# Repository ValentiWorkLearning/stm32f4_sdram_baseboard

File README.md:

# stm32f4_sdram_baseboard

The board which is based on STM32F446ZE MCU in BGA with the external SDRAM and BMI270 IMU.

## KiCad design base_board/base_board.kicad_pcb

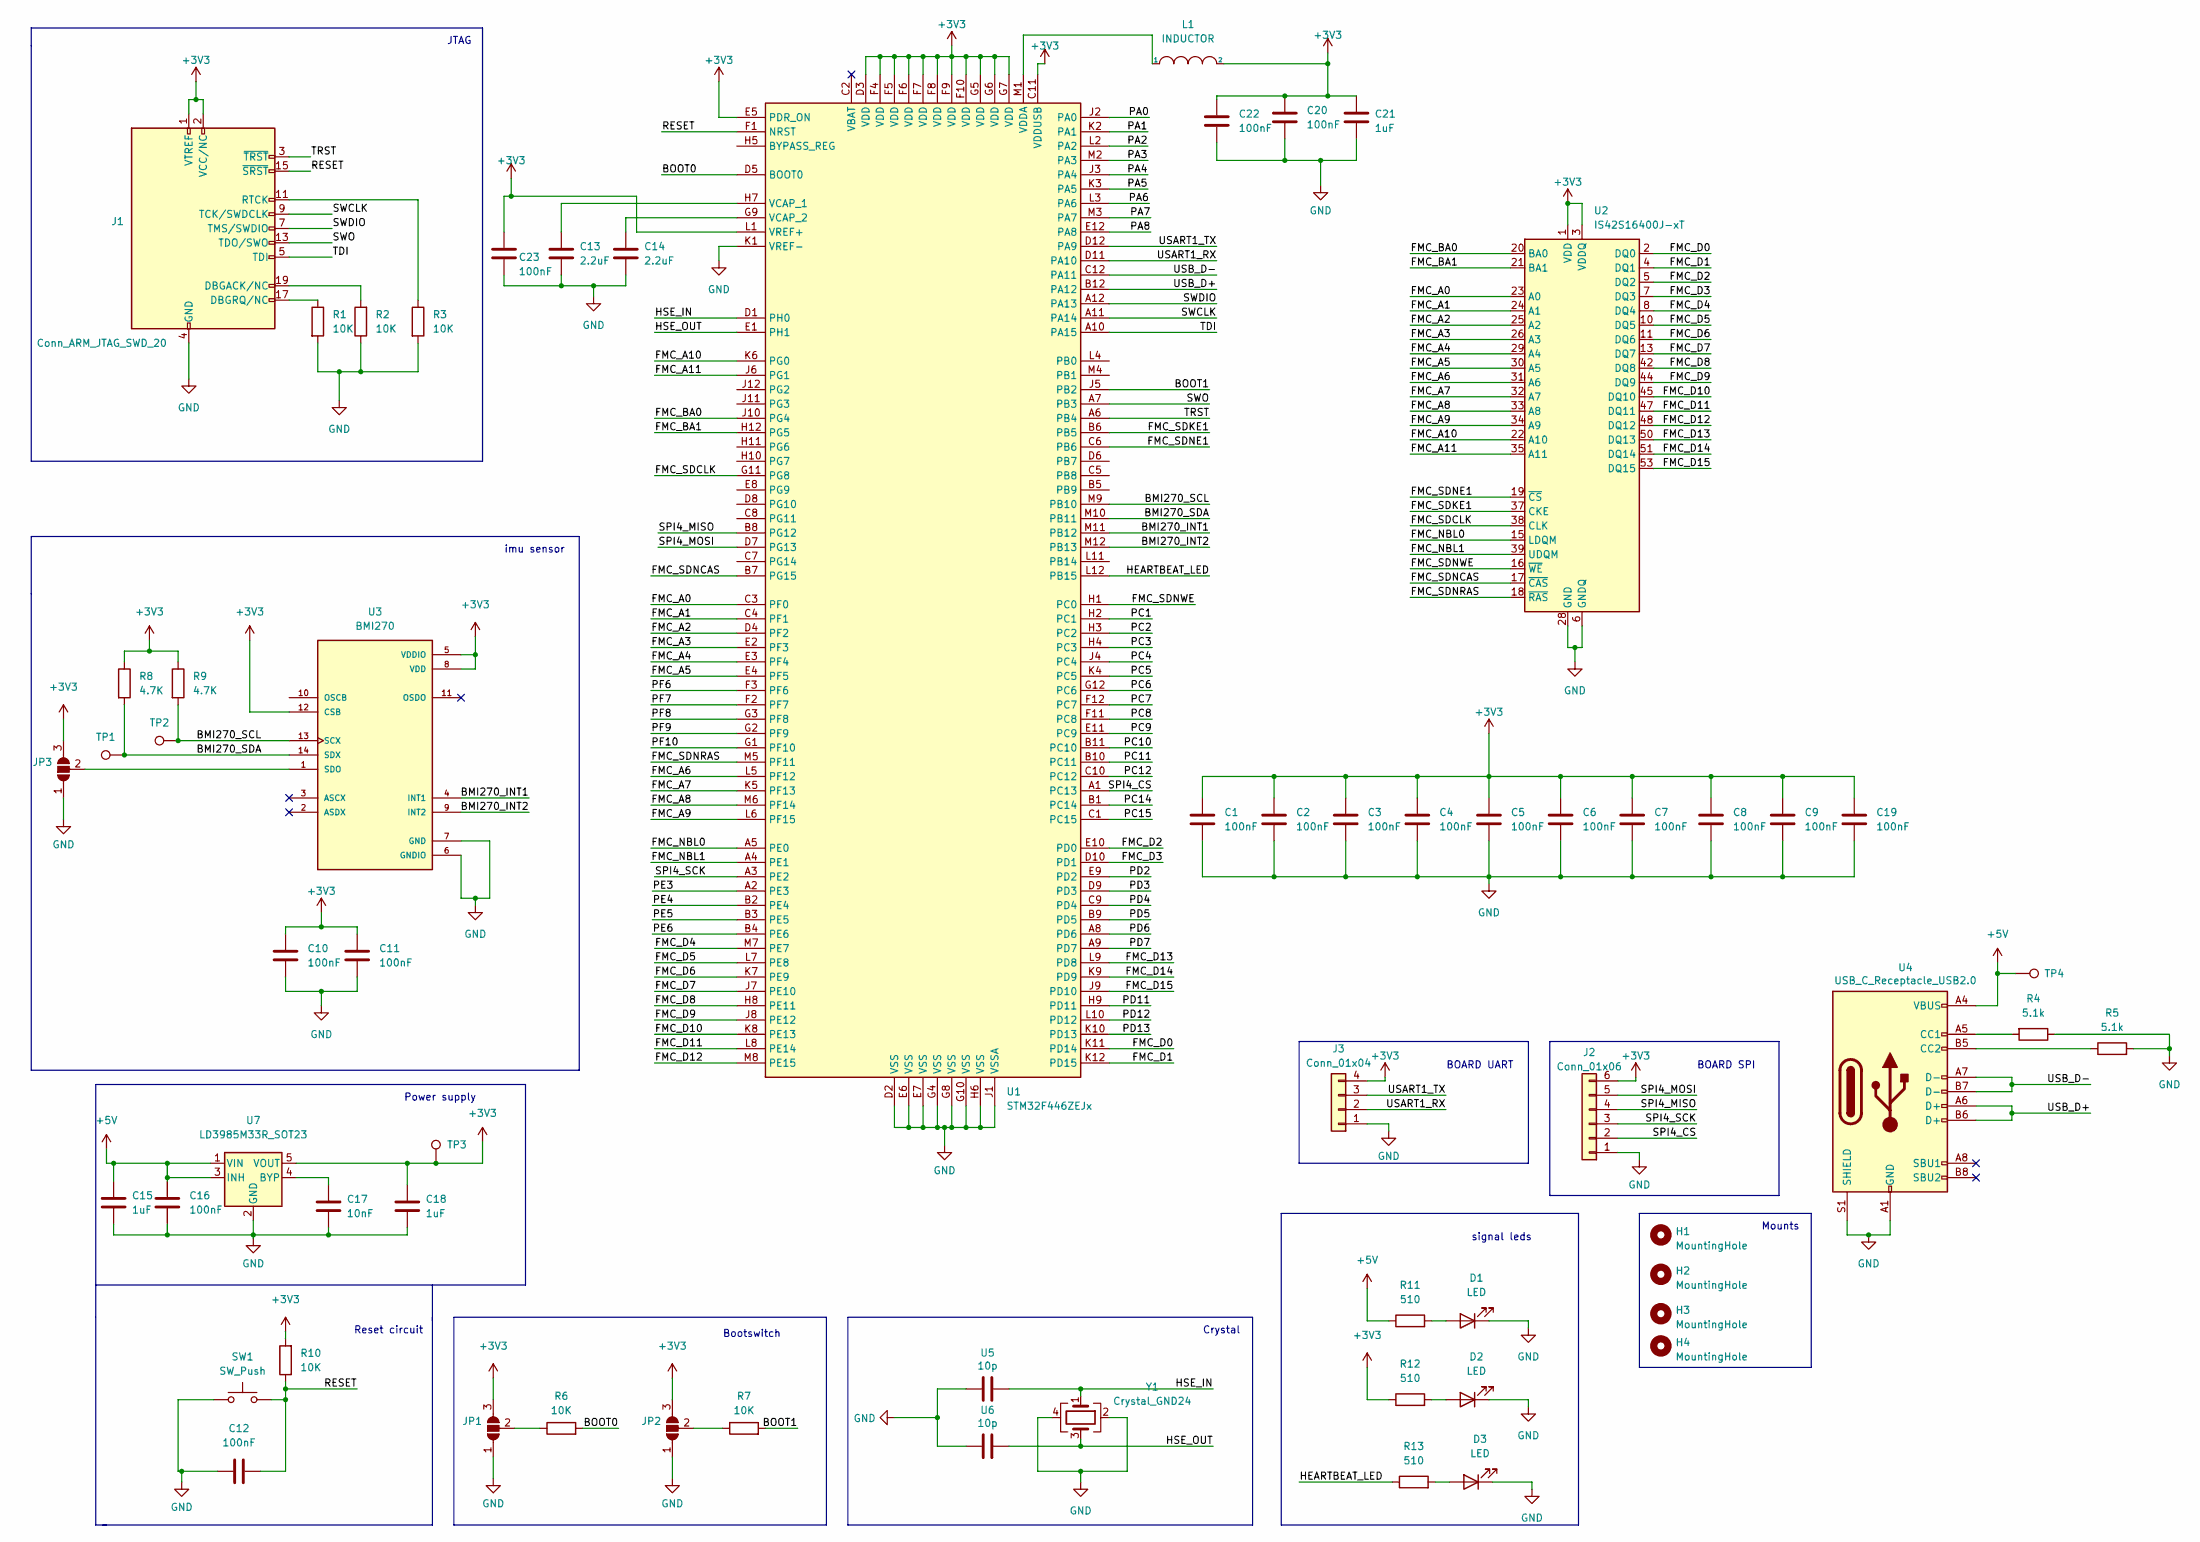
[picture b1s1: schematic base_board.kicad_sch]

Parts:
C1, C2, C3, C4, C5, C6, C7, C8, C9, C10, C11, C12, C16, C19, C20, C22, C23: 100nF; C_0603_1608Metric
C13, C14: 2.2uF; C_0603_1608Metric
C15, C18, C21: 1uF; C_0603_1608Metric
C17: 10nF; C_0603_1608Metric
D1, D2, D3: LED; LED_0603_1608Metric
H1, H2, H3, H4: MountingHole; MountingHole_3.2mm_M3
J1: Conn_ARM_JTAG_SWD_20; PinSocket_2x10_P2.54mm_Vertical
J2: Conn_01x06; PinHeader_1x06_P2.54mm_Vertical
J3: Conn_01x04; PinHeader_1x04_P2.54mm_Vertical
JP1, JP2, JP3: SolderJumper_3_Open; SolderJumper-3_P1.3mm_Open_RoundedPad1.0x1.5mm
L1: INDUCTOR; L_0603_1608Metric
R1, R2, R3, R6, R7, R10: 10K; R_0603_1608Metric
R4, R5: 5.1k; R_0603_1608Metric
R8, R9: 4.7K; R_0603_1608Metric
R11, R12, R13: 510; R_0603_1608Metric
SW1: SW_Push; SW_Push_1P1T_NO_6x6mm_H9.5mm
TP1, TP2, TP3, TP4: TestPoint; TestPoint_Pad_D3.0mm
U1: STM32F446ZEJx; UFBGA-144_10x10mm_Layout12x12_P0.8mm
U2: IS42S16400J-xT; TSOP-II-54_22.2x10.16mm_P0.8mm
U3: BMI270; XDCR_BMI270
U4: USB_C_Receptacle_USB2.0; USB_C_Receptacle_XKB_U262-16XN-4BVC11; LCSC C319148
U5, U6: 10p; C_0603_1608Metric; LCSC C32949
U7: LD3985M33R_SOT23; SOT-23-5
Y1: Crystal_GND24; Crystal_SMD_3225-4Pin_3.2x2.5mm

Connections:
+3V3: C1.1, C2.1, C3.1, C4.1, C5.1, C6.1, C7.1, C8.1, C9.1, C10.2, C11.2, C18.1, C19.1, C20.1, C21.1, C22.1, C23.1, J1.1 (VTREF), J1.2 (VCC/NC), J2.6, J3.4, JP1.3 (B), JP2.3 (B), JP3.3 (B), L1.2, R8.1, R9.1, R10.2, R12.1, TP3.1, U1.C11 (VDDUSB), U1.D3 (VDD), U1.E5 (PDR_ON), U1.F4 (VDD), U1.F5 (VDD), U1.F6 (VDD), U1.F7 (VDD), U1.F8 (VDD), U1.F9 (VDD), U1.F10 (VDD), U1.G5 (VDD), U1.G6 (VDD), U1.G7 (VDD), U1.L1 (VREF+), U2.1 (VDD), U2.3 (VDDQ), U2.9 (VDDQ), U2.14 (VDD), U2.27 (VDD), U2.43 (VDDQ), U2.49 (VDDQ), U3.5 (VDDIO), U3.8 (VDD), U3.12 (CSB), U7.5 (VOUT)
+5V: C15.1, C16.2, R11.1, TP4.1, U4.A4 (VBUS), U4.A9 (VBUS), U4.B4 (VBUS), U4.B9 (VBUS), U7.1 (VIN), U7.3 (INH)
/BMI270_INT1: U1.M11 (PB12), U3.4 (INT1)
/BMI270_INT2: U1.M12 (PB13), U3.9 (INT2)
/BMI270_SCL: R9.2, TP2.1, U1.M9 (PB10), U3.13 (SCX)
/BMI270_SDA: R8.2, TP1.1, U1.M10 (PB11), U3.14 (SDX)
/BOOT0: R6.2, U1.D5 (BOOT0)
/BOOT1: R7.2, U1.J5 (PB2)
/FMC_A0: U1.C3 (PF0), U2.23 (A0)
/FMC_A1: U1.C4 (PF1), U2.24 (A1)
/FMC_A2: U1.D4 (PF2), U2.25 (A2)
/FMC_A3: U1.E2 (PF3), U2.26 (A3)
/FMC_A4: U1.E3 (PF4), U2.29 (A4)
/FMC_A5: U1.E4 (PF5), U2.30 (A5)
/FMC_A6: U1.L5 (PF12), U2.31 (A6)
/FMC_A7: U1.K5 (PF13), U2.32 (A7)
/FMC_A8: U1.M6 (PF14), U2.33 (A8)
/FMC_A9: U1.L6 (PF15), U2.34 (A9)
/FMC_A10: U1.K6 (PG0), U2.22 (A10)
/FMC_A11: U1.J6 (PG1), U2.35 (A11)
/FMC_BA0: U1.J10 (PG4), U2.20 (BA0)
/FMC_BA1: U1.H12 (PG5), U2.21 (BA1)
/FMC_D0: U1.K11 (PD14), U2.2 (DQ0)
/FMC_D1: U1.K12 (PD15), U2.4 (DQ1)
/FMC_D2: U1.E10 (PD0), U2.5 (DQ2)
/FMC_D3: U1.D10 (PD1), U2.7 (DQ3)
/FMC_D4: U1.M7 (PE7), U2.8 (DQ4)
/FMC_D5: U1.L7 (PE8), U2.10 (DQ5)
/FMC_D6: U1.K7 (PE9), U2.11 (DQ6)
/FMC_D7: U1.J7 (PE10), U2.13 (DQ7)
/FMC_D8: U1.H8 (PE11), U2.42 (DQ8)
/FMC_D9: U1.J8 (PE12), U2.44 (DQ9)
/FMC_D10: U1.K8 (PE13), U2.45 (DQ10)
/FMC_D11: U1.L8 (PE14), U2.47 (DQ11)
/FMC_D12: U1.M8 (PE15), U2.48 (DQ12)
/FMC_D13: U1.L9 (PD8), U2.50 (DQ13)
/FMC_D14: U1.K9 (PD9), U2.51 (DQ14)
/FMC_D15: U1.J9 (PD10), U2.53 (DQ15)
/FMC_NBL0: U1.A5 (PE0), U2.15 (LDQM)
/FMC_NBL1: U1.A4 (PE1), U2.39 (UDQM)
/FMC_SDCLK: U1.G11 (PG8), U2.38 (CLK)
/FMC_SDKE1: U1.B6 (PB5), U2.37 (CKE)
/FMC_SDNCAS: U1.B7 (PG15), U2.17 (~CAS)
/FMC_SDNE1: U1.C6 (PB6), U2.19 (~CS)
/FMC_SDNRAS: U1.M5 (PF11), U2.18 (~RAS)
/FMC_SDNWE: U1.H1 (PC0), U2.16 (~WE)
/HEARTBEAT_LED: R13.1, U1.L12 (PB15)
/HSE_IN: U1.D1 (PH0), U5.1, Y1.1
/HSE_OUT: U1.E1 (PH1), U6.1, Y1.3
/PA0: U1.J2 (PA0)
/PA1: U1.K2 (PA1)
/PA2: U1.L2 (PA2)
/PA3: U1.M2 (PA3)
/PA4: U1.J3 (PA4)
/PA5: U1.K3 (PA5)
/PA6: U1.L3 (PA6)
/PA7: U1.M3 (PA7)
/PA8: U1.E12 (PA8)
/PC1: U1.H2 (PC1)
/PC2: U1.H3 (PC2)
/PC3: U1.H4 (PC3)
/PC4: U1.J4 (PC4)
/PC5: U1.K4 (PC5)
/PC6: U1.G12 (PC6)
/PC7: U1.F12 (PC7)
/PC8: U1.F11 (PC8)
/PC9: U1.E11 (PC9)
/PC10: U1.B11 (PC10)
/PC11: U1.B10 (PC11)
/PC12: U1.C10 (PC12)
/PC14: U1.B1 (PC14)
/PC15: U1.C1 (PC15)
/PD2: U1.E9 (PD2)
/PD3: U1.D9 (PD3)
/PD4: U1.C9 (PD4)
/PD5: U1.B9 (PD5)
/PD6: U1.A8 (PD6)
/PD7: U1.A9 (PD7)
/PD11: U1.H9 (PD11)
/PD12: U1.L10 (PD12)
/PD13: U1.K10 (PD13)
/PE3: U1.A2 (PE3)
/PE4: U1.B2 (PE4)
/PE5: U1.B3 (PE5)
/PE6: U1.B4 (PE6)
/PF6: U1.F3 (PF6)
/PF7: U1.F2 (PF7)
/PF8: U1.G3 (PF8)
/PF9: U1.G2 (PF9)
/PF10: U1.G1 (PF10)
/RESET: C12.1, J1.15 (~SRST), R10.1, SW1.2, U1.F1 (NRST)
/SPI4_CS: J2.2, U1.A1 (PC13)
/SPI4_MISO: J2.4, U1.B8 (PG12)
/SPI4_MOSI: J2.5, U1.D7 (PG13)
/SPI4_SCK: J2.3, U1.A3 (PE2)
/SWCLK: J1.9 (TCK/SWDCLK), U1.A11 (PA14)
/SWDIO: J1.7 (TMS/SWDIO), U1.A12 (PA13)
/SWO: J1.13 (TDO/SWO), U1.A7 (PB3)
/TDI: J1.5 (TDI), U1.A10 (PA15)
/TRST: J1.3 (~TRST), U1.A6 (PB4)
/USART1_RX: J3.2, U1.D11 (PA10)
/USART1_TX: J3.3, U1.D12 (PA9)
/USB_D+: U1.B12 (PA12), U4.A6 (D+), U4.B6 (D+)
/USB_D-: U1.C12 (PA11), U4.A7 (D-), U4.B7 (D-)
GND: C1.2, C2.2, C3.2, C4.2, C5.2, C6.2, C7.2, C8.2, C9.2, C10.1, C11.1, C12.2, C13.1, C14.1, C15.2, C16.1, C17.2, C18.2, C19.2, C20.2, C21.2, C22.2, C23.2, D1.1 (K), D2.1 (K), D3.1 (K), J1.4 (GND), J1.6 (GND), J1.8 (GND), J1.10 (GND), J1.12 (GND), J1.14 (GND), J1.16 (GND), J1.18 (GND), J1.20 (GND), J2.1, J3.1, JP1.1 (A), JP2.1 (A), JP3.1 (A), R1.2, R2.1, R3.2, R4.1, R5.2, SW1.1, U1.D2 (VSS), U1.E6 (VSS), U1.E7 (VSS), U1.G4 (VSS), U1.G8 (VSS), U1.G10 (VSS), U1.H6 (VSS), U1.J1 (VSSA), U1.K1 (VREF-), U2.6 (GNDQ), U2.12 (GNDQ), U2.28 (GND), U2.41 (GND), U2.46 (GNDQ), U2.52 (GNDQ), U2.54 (GND), U3.6 (GNDIO), U3.7 (GND), U4.A1 (GND), U4.A12 (GND), U4.B1 (GND), U4.B12 (GND), U4.S1 (SHIELD), U5.2, U6.2, U7.2 (GND), Y1.2, Y1.4
unnamed: D1.2 (A), R11.2
unnamed: D2.2 (A), R12.2
unnamed: D3.2 (A), R13.2
unnamed: J1.19 (DBGACK/NC), R2.2
unnamed: J1.17 (DBGRQ/NC), R1.1
unnamed: J1.11 (RTCK), R3.1
unnamed: JP1.2 (C), R6.1
unnamed: JP2.2 (C), R7.1
unnamed: JP3.2 (C), U3.1 (SDO)
unnamed: C13.2, U1.H7 (VCAP_1)
unnamed: C14.2, U1.G9 (VCAP_2)
unnamed: L1.1, U1.M1 (VDDA)
unnamed: R4.2, U4.A5 (CC1)
unnamed: R5.1, U4.B5 (CC2)
unnamed: C17.1, U7.4 (BYP)

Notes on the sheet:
BOARD SPI
JTAG
BOARD UART
Reset circuit
Crystal
Power supply
Mounts
imu sensor
signal leds
Bootswitch

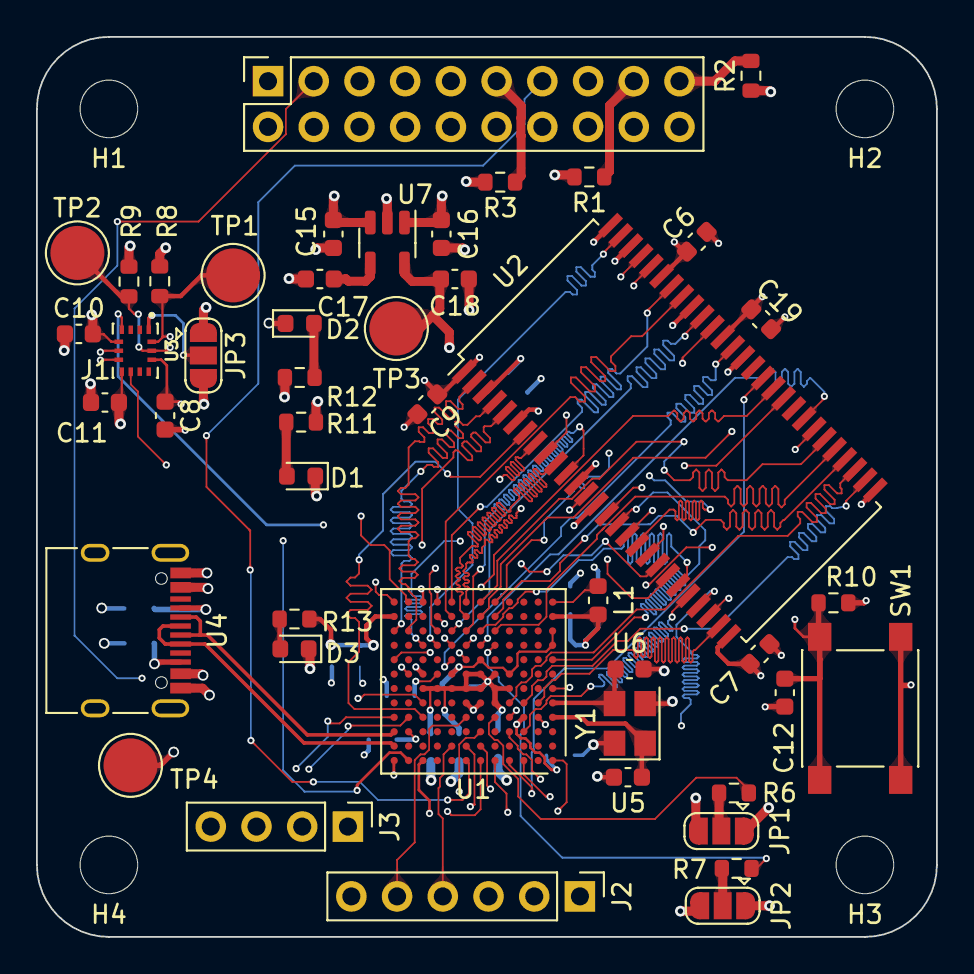
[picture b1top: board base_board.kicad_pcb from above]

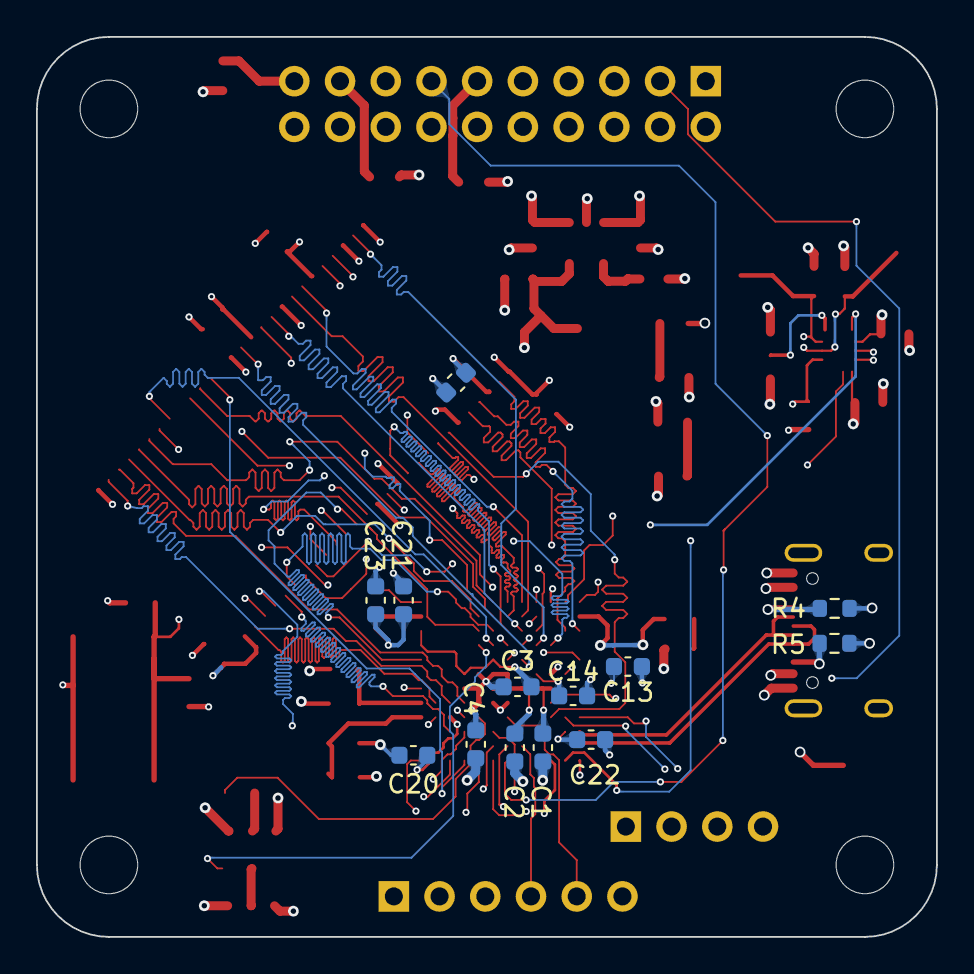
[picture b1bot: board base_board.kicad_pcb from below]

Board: 6 copper layers, 50.0 x 50.0 mm, 63 parts (13 on the bottom side), 79 nets.

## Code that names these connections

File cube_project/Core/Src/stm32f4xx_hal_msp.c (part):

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
    __HAL_RCC_GPIOB_CLK_ENABLE();
    /**I2C2 GPIO Configuration
    PB10     ------> I2C2_SCL
    PB11     ------> I2C2_SDA
    */
    GPIO_InitStruct.Pin = GPIO_PIN_10|GPIO_PIN_11;
    GPIO_InitStruct.Mode = GPIO_MODE_AF_OD;
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    __HAL_RCC_I2C2_CLK_DISABLE();

    /**I2C2 GPIO Configuration
    PB10     ------> I2C2_SCL
    PB11     ------> I2C2_SDA
    */
    HAL_GPIO_DeInit(GPIOB, GPIO_PIN_10);

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    __HAL_RCC_GPIOE_CLK_ENABLE();
    __HAL_RCC_GPIOG_CLK_ENABLE();
    /**SPI4 GPIO Configuration
    PE2     ------> SPI4_SCK
    PG12     ------> SPI4_MISO
    PG13     ------> SPI4_MOSI
    */
    GPIO_InitStruct.Pin = GPIO_PIN_2;
    GPIO_InitStruct.Mode = GPIO_MODE_AF_PP;
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    __HAL_RCC_SPI4_CLK_DISABLE();

    /**SPI4 GPIO Configuration
    PE2     ------> SPI4_SCK
    PG12     ------> SPI4_MISO
    PG13     ------> SPI4_MOSI
    */
    HAL_GPIO_DeInit(GPIOE, GPIO_PIN_2);

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
    __HAL_RCC_GPIOA_CLK_ENABLE();
    /**USART1 GPIO Configuration
    PA10     ------> USART1_RX
    PA9     ------> USART1_TX
    */
    GPIO_InitStruct.Pin = GPIO_PIN_10|GPIO_PIN_9;
    GPIO_InitStruct.Mode = GPIO_MODE_AF_PP;
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    __HAL_RCC_USART1_CLK_DISABLE();

    /**USART1 GPIO Configuration
    PA10     ------> USART1_RX
    PA9     ------> USART1_TX
    */
    HAL_GPIO_DeInit(GPIOA, GPIO_PIN_10|GPIO_PIN_9);

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
    __HAL_RCC_GPIOA_CLK_ENABLE();
    /**USB_OTG_FS GPIO Configuration
    PA12     ------> USB_OTG_FS_DP
    PA11     ------> USB_OTG_FS_DM
    */
    GPIO_InitStruct.Pin = GPIO_PIN_12|GPIO_PIN_11;
    GPIO_InitStruct.Mode = GPIO_MODE_AF_PP;
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    __HAL_RCC_USB_OTG_FS_CLK_DISABLE();

    /**USB_OTG_FS GPIO Configuration
    PA12     ------> USB_OTG_FS_DP
    PA11     ------> USB_OTG_FS_DM
    */
    HAL_GPIO_DeInit(GPIOA, GPIO_PIN_12|GPIO_PIN_11);

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  __HAL_RCC_FMC_CLK_ENABLE();

  /** FMC GPIO Configuration
  PE1   ------> FMC_NBL1
  PE0   ------> FMC_NBL0
  PB5   ------> FMC_SDCKE1
  PG15   ------> FMC_SDNCAS
  PF0   ------> FMC_A0
  PF1   ------> FMC_A1
  PB6   ------> FMC_SDNE1
  PF2   ------> FMC_A2
  PD1   ------> FMC_D3
  PF3   ------> FMC_A3
  PF4   ------> FMC_A4
  PF5   ------> FMC_A5
  PD0   ------> FMC_D2
  PG8   ------> FMC_SDCLK
  PC0   ------> FMC_SDNWE
  PE11   ------> FMC_D8
  PG5   ------> FMC_BA1
  PG1   ------> FMC_A11
  PE10   ------> FMC_D7
  PE12   ------> FMC_D9
  PD10   ------> FMC_D15
  PG4   ------> FMC_BA0
  PF13   ------> FMC_A7
  PG0   ------> FMC_A10
  PE9   ------> FMC_D6
  PE13   ------> FMC_D10
  PD9   ------> FMC_D14
  PD14   ------> FMC_D0
  PD15   ------> FMC_D1
  PF12   ------> FMC_A6
  PF15   ------> FMC_A9
  PE8   ------> FMC_D5
  PE14   ------> FMC_D11
  PD8   ------> FMC_D13
  PF11   ------> FMC_SDNRAS
  PF14   ------> FMC_A8
  PE7   ------> FMC_D4
  PE15   ------> FMC_D12
  */
  GPIO_InitStruct.Pin = GPIO_PIN_1|GPIO_PIN_0|GPIO_PIN_11|GPIO_PIN_10
                          |GPIO_PIN_12|GPIO_PIN_9|GPIO_PIN_13|GPIO_PIN_8
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  __HAL_RCC_FMC_CLK_DISABLE();

  /** FMC GPIO Configuration
  PE1   ------> FMC_NBL1
  PE0   ------> FMC_NBL0
  PB5   ------> FMC_SDCKE1
  PG15   ------> FMC_SDNCAS
  PF0   ------> FMC_A0
  PF1   ------> FMC_A1
  PB6   ------> FMC_SDNE1
  PF2   ------> FMC_A2
  PD1   ------> FMC_D3
  PF3   ------> FMC_A3
  PF4   ------> FMC_A4
  PF5   ------> FMC_A5
  PD0   ------> FMC_D2
  PG8   ------> FMC_SDCLK
  PC0   ------> FMC_SDNWE
  PE11   ------> FMC_D8
  PG5   ------> FMC_BA1
  PG1   ------> FMC_A11
  PE10   ------> FMC_D7
  PE12   ------> FMC_D9
  PD10   ------> FMC_D15
  PG4   ------> FMC_BA0
  PF13   ------> FMC_A7
  PG0   ------> FMC_A10
  PE9   ------> FMC_D6
  PE13   ------> FMC_D10
  PD9   ------> FMC_D14
  PD14   ------> FMC_D0
  PD15   ------> FMC_D1
  PF12   ------> FMC_A6
  PF15   ------> FMC_A9
  PE8   ------> FMC_D5
  PE14   ------> FMC_D11
  PD8   ------> FMC_D13
  PF11   ------> FMC_SDNRAS
  PF14   ------> FMC_A8
  PE7   ------> FMC_D4
  PE15   ------> FMC_D12
  */
  HAL_GPIO_DeInit(GPIOE, GPIO_PIN_1|GPIO_PIN_0|GPIO_PIN_11|GPIO_PIN_10
                          |GPIO_PIN_12|GPIO_PIN_9|GPIO_PIN_13|GPIO_PIN_8
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
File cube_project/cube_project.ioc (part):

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Mcu.Name=STM32F446Z(C-E)Jx
Mcu.Package=UFBGA144
Mcu.UserName=STM32F446ZEJx
PA10.Mode=Asynchronous
PA10.Signal=USART1_RX
PA11.Mode=Device_Only
PA11.Signal=USB_OTG_FS_DM
PA12.Mode=Device_Only
PA12.Signal=USB_OTG_FS_DP
PA13.Mode=Serial_Wire
PA13.Signal=SYS_JTMS-SWDIO
PA14.Mode=Serial_Wire
PA14.Signal=SYS_JTCK-SWCLK
PA9.Mode=Asynchronous
PA9.Signal=USART1_TX
PB10.Mode=I2C
PB10.Signal=I2C2_SCL
PB11.Mode=I2C
PB11.Signal=I2C2_SDA
PB12.GPIOParameters=GPIO_Label
PB12.GPIO_Label=BMI270_INT1
PB12.Signal=GPXTI12
PB13.GPIOParameters=GPIO_Label
PB13.GPIO_Label=BMI270_INT2
PB13.Signal=GPXTI13
PB15.GPIOParameters=GPIO_Label
PB15.GPIO_Label=HEARTBEAT_LED
PB15.Signal=GPIO_Output
PB5.Mode=SdramChipSelect2_1
PB5.Signal=FMC_SDCKE1
PB6.Mode=SdramChipSelect2_1
PB6.Signal=FMC_SDNE1
PC0.Signal=FMC_SDNWE
PC13.GPIOParameters=GPIO_Label
PC13.GPIO_Label=SPI4_CUSTOM_CS
PC13.Signal=GPIO_Output
PD0.Signal=FMC_D2_DA2
PD1.Signal=FMC_D3_DA3
PD10.Signal=FMC_D15_DA15
PD14.Signal=FMC_D0_DA0
PD15.Signal=FMC_D1_DA1
PD8.Signal=FMC_D13_DA13
PD9.Signal=FMC_D14_DA14
PE0.Signal=FMC_NBL0
PE1.Signal=FMC_NBL1
PE10.Signal=FMC_D7_DA7
PE11.Signal=FMC_D8_DA8
PE12.Signal=FMC_D9_DA9
PE13.Signal=FMC_D10_DA10
PE14.Signal=FMC_D11_DA11
PE15.Signal=FMC_D12_DA12
PE2.Mode=Full_Duplex_Master
PE2.Signal=SPI4_SCK
PE7.Signal=FMC_D4_DA4
PE8.Signal=FMC_D5_DA5
PE9.Signal=FMC_D6_DA6
PF0.Signal=FMC_A0
PF1.Signal=FMC_A1
PF11.Signal=FMC_SDNRAS
PF12.Signal=FMC_A6
PF13.Signal=FMC_A7
PF14.Signal=FMC_A8
PF15.Signal=FMC_A9
PF2.Signal=FMC_A2
PF3.Signal=FMC_A3
PF4.Signal=FMC_A4
PF5.Signal=FMC_A5
PG0.Signal=FMC_A10
PG1.Signal=FMC_A11
PG12.Mode=Full_Duplex_Master
PG12.Signal=SPI4_MISO
PG13.Mode=Full_Duplex_Master
PG13.Signal=SPI4_MOSI
PG15.Signal=FMC_SDNCAS
PG4.Signal=FMC_A14_BA0
PG5.Signal=FMC_A15_BA1
PG8.Signal=FMC_SDCLK
PH0-OSC_IN.Mode=HSE-External-Oscillator
PH0-OSC_IN.Signal=RCC_OSC_IN
PH1-OSC_OUT.Mode=HSE-External-Oscillator
PH1-OSC_OUT.Signal=RCC_OSC_OUT
RCC.HSE_VALUE=8000000
RCC.SYSCLKFreq_VALUE=168000000
RCC.SYSCLKSource=RCC_SYSCLKSOURCE_PLLCLK
board=custom

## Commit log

2022-12-18 [schematic][pcb] initial commit
2022-12-29 [pcb][cube][schematic] added SWD, Crystal, USB
2023-01-04 [schematic][pcb] added usb, signal leds, LDO
2023-02-28 [pcb][schematic] fixed sdram connection. added 6 layers stack
2023-02-28 [pcb] draft of components layout
2023-03-02 [pcb] changed capacitors layer
2023-03-03 [pcb][schematic] removed libraries root dependency
2023-03-03 [pcb][schematic] added gpio headers&sockets
2023-03-03 [pcb] added part of bga route
2023-03-03 [pcb] added more bga routing
2023-03-04 [pcb] draft route of SDRAM
2023-03-04 [pcb] corrected missed SDRAM trace
2023-03-04 [pcb] draft length match for SDRAM
2023-03-04 [pcb] added route for BMI270
2023-03-04 [pcb] completed sdram routing
2023-03-04 [pcb] added heartbeat led traces
2023-03-05 [pcb] completed routing except VDDUSB
2023-03-06 [pcb] changed routing for 5V power bus
2023-03-07 [pcb] fixed drc violation
2023-03-07 [pcb] added caps for VDDUSB
2023-03-07 [pcb] draft length matching
2023-03-08 [pcb] fixed length matching for sdram memory
2023-03-08 [view][pcb] toggled all layers for pcb
2023-03-08 [pcb] fixed power planes. Fixed traces shape
2023-03-14 [pcb] added review corrections
2023-03-14 [pcb] added M3 holes
2023-03-14 [pcb] added onboard uart
2023-03-17 [pcb] added gnd+3v3 for uart socket
2023-03-17 [pcb][schematic] fixed VREF connection. Corrected the shape of the length matcher
2023-03-17 [project] updated fp-info-cache
2023-03-18 [pcb] fixed length matching pattern
2023-03-18 [pcb] placed sdram chip at 45 degree angle
2023-03-21 [project] updated fp-info cache
2023-03-21 Implemented SDRAM routing (#1)
    * [pcb] completed sdram routing
    * [pcb] added heartbeat led traces
    * [pcb] completed routing except VDDUSB
    * [pcb] changed routing for 5V power bus
    * [pcb] fixed drc violation
    * [pcb] added caps for VDDUSB
2023-03-21 [pcb] cleanup of sdram routing
2023-03-21 [pcb] moved sdram chip to the same layer with mcu
2023-03-21 [pcb] draft of length matching implementation
2023-03-21 [pcb] implemented length matching for SDRAM on the same layer with MCU
2023-03-22 Implementation of SDRAM routing with placement it on the same layer with MCU (#3)
    * [pcb] cleanup of sdram routing
    * [pcb] moved sdram chip to the same layer with mcu
    * [pcb] draft of length matching implementation
    * [pcb] implemented length matching for SDRAM on the same layer with MCU
2023-03-23 [pcb][schematic] added draft for SPI routing& schematic with CubeMX
2023-03-23 [pcb][schematic] added SPI header for the board(#4)
2023-03-25 [pcb] added teardrops
2023-03-25 [pcb] added teardrops (#7)
2023-03-26 [project] update fp-info-cache
2023-03-26 [pcb] corrected board stackup according to JLC06161H-3313
2023-03-26 [pcb] corrected board stackup according to JLC06161H-3313 (#8)
2023-03-30 [pcb] fixed final review comments
2023-03-31 [pcb] fixed final review comments (#10)
2023-03-31 [fabrication] added fabrication output
2023-03-31 [sw] added software architecture
2023-04-01 [fabrication] fixed remarks from JLCPCB mailiing
2023-04-28 Added SDRAM test with updated cube project
2023-04-28 Added bmi270 testing code
2023-04-28 Implementation of draft test firmware for the SDRAM and I2C (#13)
    * Added SDRAM test with updated cube project
    * Added bmi270 testing code
2023-04-28 Added initial rust blinker
2023-05-01 Added draft sdram
2023-05-01 Added board 3D STEP. Added missed USB-C connector.
2023-05-29 Moved sensor to hierarchical sheet

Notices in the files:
cube_project/Core/Src/stm32f4xx_hal_msp.c:
Copyright (c) 2023 STMicroelectronics.
All rights reserved.
This software is licensed under terms that can be found in the LICENSE file
